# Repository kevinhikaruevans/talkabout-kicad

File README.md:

# talkabout-kicad
KiCAD designs

## Keyboard

Uses a 6-input, 6-output scanning grid. Need to remove the silkscreen and cleanup some stuff. I should eventually change the routing, since some of the routes are ugly.

Alignment is okay, it required a little filing to get it to fit:

This will be fine for testing and getting the scanning functionality working, but I think I will switch to a lower-profile surface-mount connector.

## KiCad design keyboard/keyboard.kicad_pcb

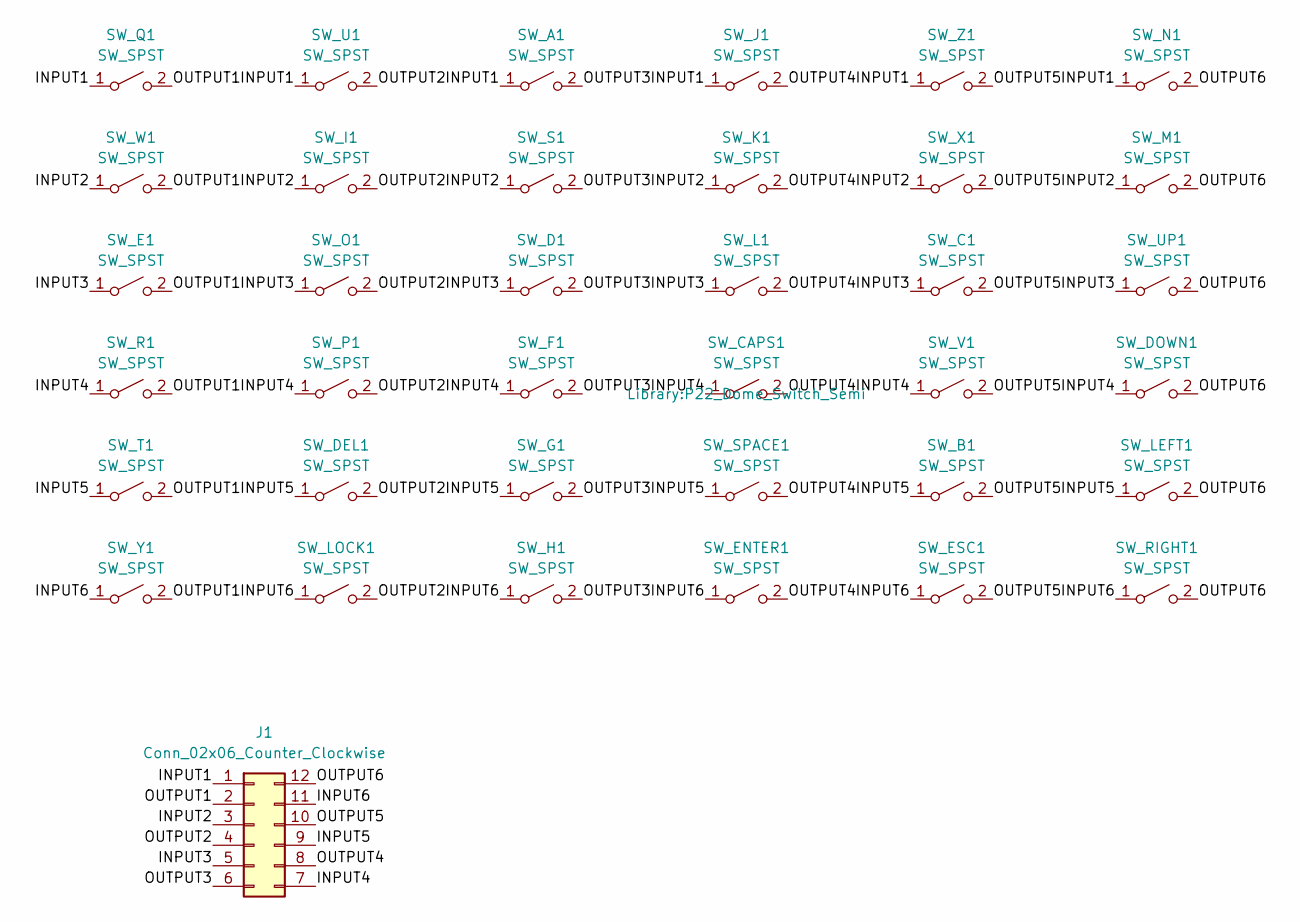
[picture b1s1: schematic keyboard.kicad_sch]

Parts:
J1: Conn_02x06_Counter_Clockwise; PinHeader_2x06_P2.54mm_Vertical_SMD
SW_A1: SW_SPST; P22_Dome_Switch
SW_B1: SW_SPST; P22_Dome_Switch
SW_C1: SW_SPST; P22_Dome_Switch
SW_CAPS1: SW_SPST; P22_Dome_Switch_Semi
SW_D1: SW_SPST; P22_Dome_Switch
SW_DEL1: SW_SPST; P22_Dome_Switch
SW_DOWN1: SW_SPST; P22_Dome_Switch_Semi
SW_E1: SW_SPST; P22_Dome_Switch
SW_ENTER1: SW_SPST; P22_Dome_Switch_Semi
SW_ESC1: SW_SPST; P22_Dome_Switch
SW_F1: SW_SPST; P22_Dome_Switch
SW_G1: SW_SPST; P22_Dome_Switch
SW_H1: SW_SPST; P22_Dome_Switch
SW_I1: SW_SPST; P22_Dome_Switch
SW_J1: SW_SPST; P22_Dome_Switch
SW_K1: SW_SPST; P22_Dome_Switch
SW_L1: SW_SPST; P22_Dome_Switch
SW_LEFT1: SW_SPST; P22_Dome_Switch
SW_LOCK1: SW_SPST; P22_Dome_Switch
SW_M1: SW_SPST; P22_Dome_Switch
SW_N1: SW_SPST; P22_Dome_Switch
SW_O1: SW_SPST; P22_Dome_Switch
SW_P1: SW_SPST; P22_Dome_Switch
SW_Q1: SW_SPST; P22_Dome_Switch
SW_R1: SW_SPST; P22_Dome_Switch
SW_RIGHT1: SW_SPST; P22_Dome_Switch
SW_S1: SW_SPST; P22_Dome_Switch
SW_SPACE1: SW_SPST; P22_Dome_Switch_Semi
SW_T1: SW_SPST; P22_Dome_Switch
SW_U1: SW_SPST; P22_Dome_Switch
SW_UP1: SW_SPST; P22_Dome_Switch
SW_V1: SW_SPST; P22_Dome_Switch
SW_W1: SW_SPST; P22_Dome_Switch
SW_X1: SW_SPST; P22_Dome_Switch
SW_Y1: SW_SPST; P22_Dome_Switch
SW_Z1: SW_SPST; P22_Dome_Switch

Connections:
/INPUT1: J1.1, SW_A1.1 (A), SW_J1.1 (A), SW_N1.1 (A), SW_Q1.1 (A), SW_U1.1 (A), SW_Z1.1 (A)
/INPUT2: J1.3, SW_I1.1 (A), SW_K1.1 (A), SW_M1.1 (A), SW_S1.1 (A), SW_W1.1 (A), SW_X1.1 (A)
/INPUT3: J1.5, SW_C1.1 (A), SW_D1.1 (A), SW_E1.1 (A), SW_L1.1 (A), SW_O1.1 (A), SW_UP1.1 (A)
/INPUT4: J1.7, SW_CAPS1.1 (A), SW_DOWN1.1 (A), SW_F1.1 (A), SW_P1.1 (A), SW_R1.1 (A), SW_V1.1 (A)
/INPUT5: J1.9, SW_B1.1 (A), SW_DEL1.1 (A), SW_G1.1 (A), SW_LEFT1.1 (A), SW_SPACE1.1 (A), SW_T1.1 (A)
/INPUT6: J1.11, SW_ENTER1.1 (A), SW_ESC1.1 (A), SW_H1.1 (A), SW_LOCK1.1 (A), SW_RIGHT1.1 (A), SW_Y1.1 (A)
/OUTPUT1: J1.2, SW_E1.2 (B), SW_Q1.2 (B), SW_R1.2 (B), SW_T1.2 (B), SW_W1.2 (B), SW_Y1.2 (B)
/OUTPUT2: J1.4, SW_DEL1.2 (B), SW_I1.2 (B), SW_LOCK1.2 (B), SW_O1.2 (B), SW_P1.2 (B), SW_U1.2 (B)
/OUTPUT3: J1.6, SW_A1.2 (B), SW_D1.2 (B), SW_F1.2 (B), SW_G1.2 (B), SW_H1.2 (B), SW_S1.2 (B)
/OUTPUT4: J1.8, SW_CAPS1.2 (B), SW_ENTER1.2 (B), SW_J1.2 (B), SW_K1.2 (B), SW_L1.2 (B), SW_SPACE1.2 (B)
/OUTPUT5: J1.10, SW_B1.2 (B), SW_C1.2 (B), SW_ESC1.2 (B), SW_V1.2 (B), SW_X1.2 (B), SW_Z1.2 (B)
/OUTPUT6: J1.12, SW_DOWN1.2 (B), SW_LEFT1.2 (B), SW_M1.2 (B), SW_N1.2 (B), SW_RIGHT1.2 (B), SW_UP1.2 (B)

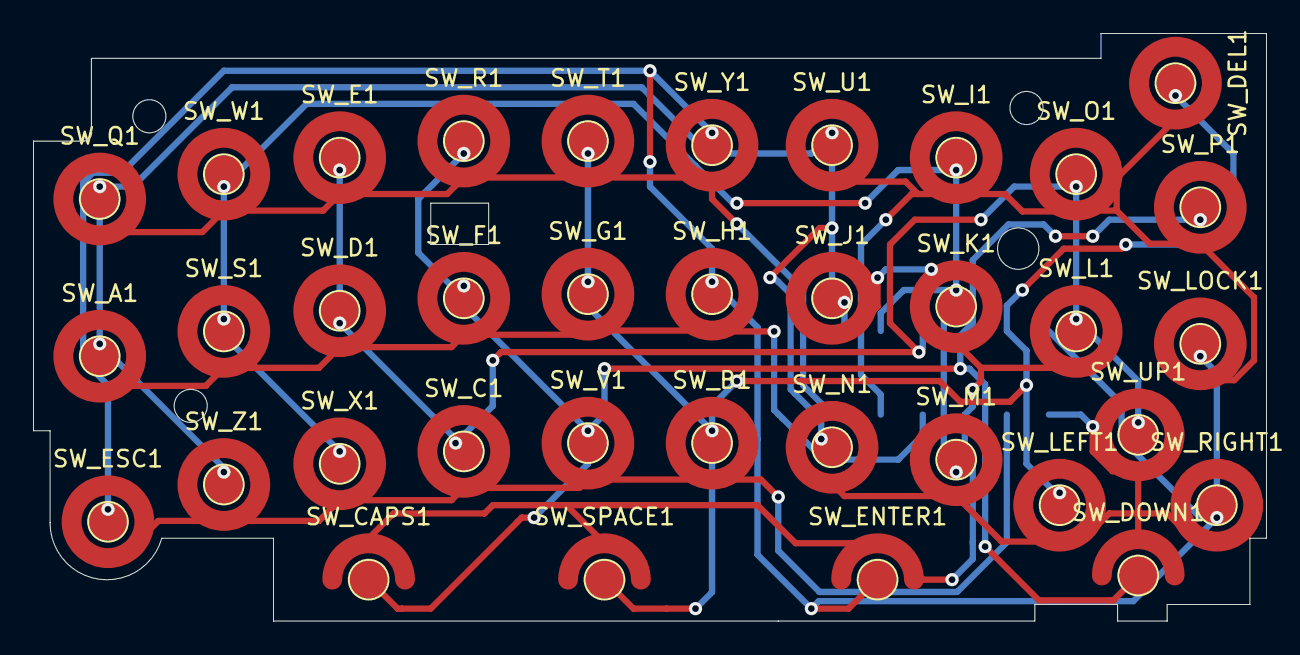
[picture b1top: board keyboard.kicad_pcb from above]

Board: 2 copper layers, 74.5 x 35.5 mm, 37 parts (1 on the bottom side), 12 nets.
